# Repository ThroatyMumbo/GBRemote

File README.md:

# (WIP) Universal Remote cartridge for Game Boy

A cartridge that lets you turn your Game Boy into many different things.
A game controller? A Bluetooth gamepad? A Bluetooth receiver? A tooth brush? Whatever your heart desires!

YouTube video: https://youtu.be/3ZZjWmHPqLs

Both the hardware and core GBC firmware is based on Shilga's Croco Cart:
- https://github.com/shilga/rp2350-gameboy-cartridge-firmware/
- https://github.com/shilga/rp-gameboy-cartridge-hw

## Building

Needs [GBDK-2020](https://github.com/gbdk-2020/gbdk-2020), the [Pico SDK](https://github.com/raspberrypi/pico-sdk) and Python 3.

```
python3 -m venv .venv && .venv/bin/pip install numpy
make -C rom GBDK_HOME=/path/to/gbdk
PICO_SDK_PATH=/path/to/pico-sdk cmake -S firmware -B firmware/build
cmake --build firmware/build
```

The first `make` builds the Game Boy ROM and embeds it in the firmware (`firmware/generated/rom.h`), so rebuild both after changing the ROM.

## Flashing

Hold the BOOTSEL button (`SW2`) while plugging the cartridge's micro-USB port into your computer, then either copy `firmware/build/gbc_controller.uf2` to the drive that appears or run:

```
picotool load -x firmware/build/gbc_controller.uf2
```

## Loading Game Boy ROMs for the Transfer Pak

The N64 driver can act as a Transfer Pak holding a Game Boy ROM stored in the cart's flash. Put the cart in BOOTSEL as above, then:

```
tools/slot.sh 1 game.gbc
```

Pick the game under Controllers → Nintendo 64 → Transfer Pak. Slots 1-6 hold up to 2 MB each and slot 7 up to 1.75 MB; loading one slot leaves the others alone. An optional third argument sets the name shown on the Game Boy.

## Screenshots

| Controller select | Gamepad | Button mapping |
|:---:|:---:|:---:|
|  |  |  |
| **N64 Transfer Pak** | **Dreamcast VMU** | |
|  |  | |

## FAQ

### What the hell is this?

It's a Game Boy cartridge with a bunch of stuff attached to it. USB, Bluetooth, WiFi, IR, even a generic 12-pin controller port via USB-C.

### Is this a flash cart?

Sort of. It can be used as a flash cart, although that isn't the intended purpose. It's more meant for turning a Game Boy Color into a multipurpose remote of sorts.
Plus the onboard flash is 16 MB, which is only enough for like 10 GBC games.

### Where are all those cool demos you showed in the video?

Most of them I probably won't publish since they involve modding existing commercial games, which is messy to maintain in a public repo.
However, original stuff like "Shellack!" will be published at some point when I get a chance to clean it up.

### Does this work on a regular Game Boy? What about Game Boy Advance?

- Regular Game Boy is a maybe. It doesn't physically fit, but you can cleverly bypass this using a Game Shark. However when I tried this myself it just sits on a blank screen. Haven't troubleshooted this problem.
- It does work on a Game Boy Advance

### Where do I buy this?

You can't, at least not directly. This repo contains the production files for the cartridge and adapter PCBs that you can send off to your favorite PCB manufacturing site, but I warn you it'll likely be very expensive (~$500+). Getting just two of these cartridges + 10 adapters made took a couple weeks and lots of back and forth with JLCPCB. Not to mention the tedium of wiring all those controller adapters. I wouldn't recommend it unless you have time and money to burn.

### Will you sell these at some point?

Maybe? Like every project of mine, this is really more of a novelty than something that's practically useful, so I don't see myself ordering hundreds of these and selling them on Ko-fi anytime soon. More likely a very limited run as some special merch or something.

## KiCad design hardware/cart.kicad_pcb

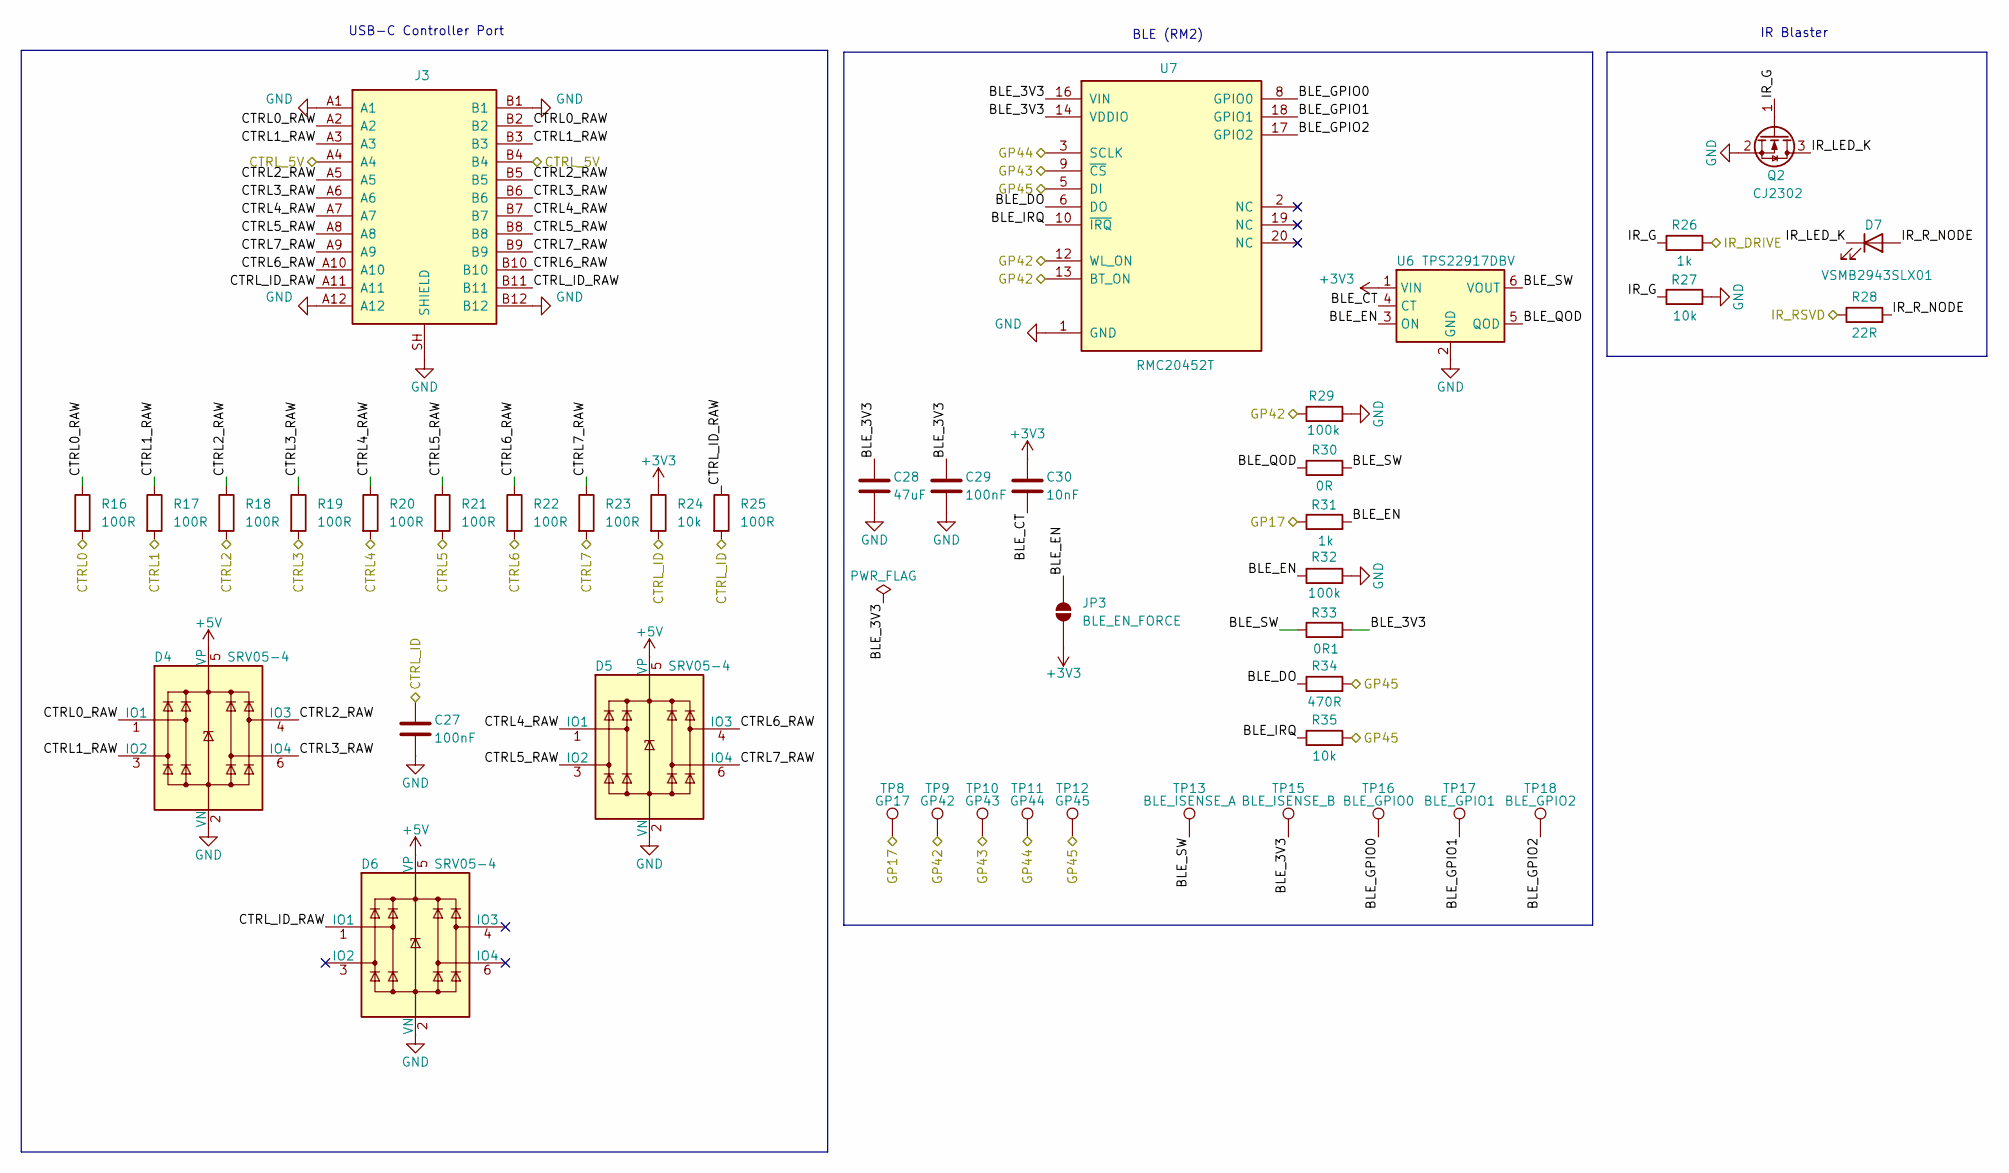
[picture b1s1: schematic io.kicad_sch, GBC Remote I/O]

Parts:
C27, C29: 100nF; C_0402_1005Metric; LCSC C1525
C28: 47uF; C_1206_3216Metric; LCSC C96123
C30: 10nF; C_0402_1005Metric; LCSC C15195
D4, D5, D6: SRV05-4; SOT-23-6; LCSC C13612
D7: VSMB2943SLX01; LED_Vishay_VSMB2943SL; LCSC C511094
J3: 12401610E4#2A; USB_C_Receptacle_Amphenol_12401610E4-2A; LCSC C5119948
JP3: BLE_EN_FORCE; SolderJumper-2_P1.3mm_Open_RoundedPad1.0x1.5mm
Q2: CJ2302; SOT-23; LCSC C8548
R16, R17, R18, R19, R20, R21, R22, R23, R25: 100R; R_0402_1005Metric; LCSC C25076
R24, R27, R35: 10k; R_0402_1005Metric; LCSC C25744
R26, R31: 1k; R_0402_1005Metric; LCSC C11702
R28: 22R; R_1206_3216Metric; LCSC C17958
R29, R32: 100k; R_0402_1005Metric; LCSC C25741
R30: 0R; R_0402_1005Metric; LCSC C17168
R33: 0R1; R_1206_3216Metric; LCSC C25334
R34: 470R; R_0402_1005Metric; LCSC C25117
TP8: GP17; TestPoint_Pad_D1.0mm
TP9: GP42; TestPoint_Pad_D1.0mm
TP10: GP43; TestPoint_Pad_D1.0mm
TP11: GP44; TestPoint_Pad_D1.0mm
TP12: GP45; TestPoint_Pad_D1.0mm
TP13: BLE_ISENSE_A; TestPoint_Pad_D1.0mm
TP15: BLE_ISENSE_B; TestPoint_Pad_D1.0mm
TP16: BLE_GPIO0; TestPoint_Pad_D1.0mm
TP17: BLE_GPIO1; TestPoint_Pad_D1.0mm
TP18: BLE_GPIO2; TestPoint_Pad_D1.0mm
U6: TPS22917DBV; SOT-23-6; LCSC C2681320
U7: RMC20452T; RaspberryPi_RM2; LCSC C49451547

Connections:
+3V3: C30.1, JP3.1 (A), R24.1, U6.1 (VIN); also elsewhere on the board
+5V: D4.5 (VP), D5.5 (VP), D6.5 (VP); also elsewhere on the board
/CTRL0: R16.2; also elsewhere on the board
/CTRL1: R17.2; also elsewhere on the board
/CTRL2: R18.2; also elsewhere on the board
/CTRL3: R19.2; also elsewhere on the board
/CTRL4: R20.2; also elsewhere on the board
/CTRL5: R21.2; also elsewhere on the board
/CTRL6: R22.2; also elsewhere on the board
/CTRL7: R23.2; also elsewhere on the board
/CTRL_5V: J3.A4, J3.B4; also elsewhere on the board
/CTRL_ID: C27.1, R24.2, R25.2; also elsewhere on the board
/Controller Port, IR, BLE/BLE_3V3: C28.1, C29.1, R33.2, TP15.1, U7.14 (VDDIO), U7.16 (VIN)
/Controller Port, IR, BLE/BLE_CT: C30.2, U6.4 (CT)
/Controller Port, IR, BLE/BLE_DO: R34.1, U7.6 (DO)
/Controller Port, IR, BLE/BLE_EN: JP3.2 (B), R31.2, R32.1, U6.3 (ON)
/Controller Port, IR, BLE/BLE_GPIO0: TP16.1, U7.8 (GPIO0)
/Controller Port, IR, BLE/BLE_GPIO1: TP17.1, U7.18 (GPIO1)
/Controller Port, IR, BLE/BLE_GPIO2: TP18.1, U7.17 (GPIO2)
/Controller Port, IR, BLE/BLE_IRQ: R35.1, U7.10 (~IRQ)
/Controller Port, IR, BLE/BLE_QOD: R30.1, U6.5 (QOD)
/Controller Port, IR, BLE/BLE_SW: R30.2, R33.1, TP13.1, U6.6 (VOUT)
/Controller Port, IR, BLE/CTRL0_RAW: D4.1 (IO1), J3.A2, J3.B2, R16.1
/Controller Port, IR, BLE/CTRL1_RAW: D4.3 (IO2), J3.A3, J3.B3, R17.1
/Controller Port, IR, BLE/CTRL2_RAW: D4.4 (IO3), J3.A5, J3.B5, R18.1
/Controller Port, IR, BLE/CTRL3_RAW: D4.6 (IO4), J3.A6, J3.B6, R19.1
/Controller Port, IR, BLE/CTRL4_RAW: D5.1 (IO1), J3.A7, J3.B7, R20.1
/Controller Port, IR, BLE/CTRL5_RAW: D5.3 (IO2), J3.A8, J3.B8, R21.1
/Controller Port, IR, BLE/CTRL6_RAW: D5.4 (IO3), J3.A10, J3.B10, R22.1
/Controller Port, IR, BLE/CTRL7_RAW: D5.6 (IO4), J3.A9, J3.B9, R23.1
/Controller Port, IR, BLE/CTRL_ID_RAW: D6.1 (IO1), J3.A11, J3.B11, R25.1
/Controller Port, IR, BLE/IR_G: Q2.1 (G), R26.1, R27.1
/Controller Port, IR, BLE/IR_LED_K: D7.1 (K), Q2.3 (D)
/Controller Port, IR, BLE/IR_R_NODE: D7.2 (A), R28.2
/GP17: R31.1, TP8.1; also elsewhere on the board
/GP42: R29.1, TP9.1, U7.12 (WL_ON), U7.13 (BT_ON); also elsewhere on the board
/GP43: TP10.1, U7.9 (~CS); also elsewhere on the board
/GP44: TP11.1, U7.3 (SCLK); also elsewhere on the board
/GP45: R34.2, R35.2, TP12.1, U7.5 (DI); also elsewhere on the board
/IR_DRIVE: R26.2; also elsewhere on the board
/IR_RSVD: R28.1; also elsewhere on the board
GND: C27.2, C28.2, C29.2, D4.2 (VN), D5.2 (VN), D6.2 (VN), J3.A1, J3.A12, J3.B1, J3.B12, J3.SH (SHIELD), Q2.2 (S), R27.2, R29.2, R32.2, U6.2 (GND), U7.1 (GND), U7.4 (GND), U7.7 (GND), U7.11 (GND), U7.15 (GND), U7.21 (GND); also elsewhere on the board

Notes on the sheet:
IR Blaster
BLE (RM2)
USB-C Controller Port

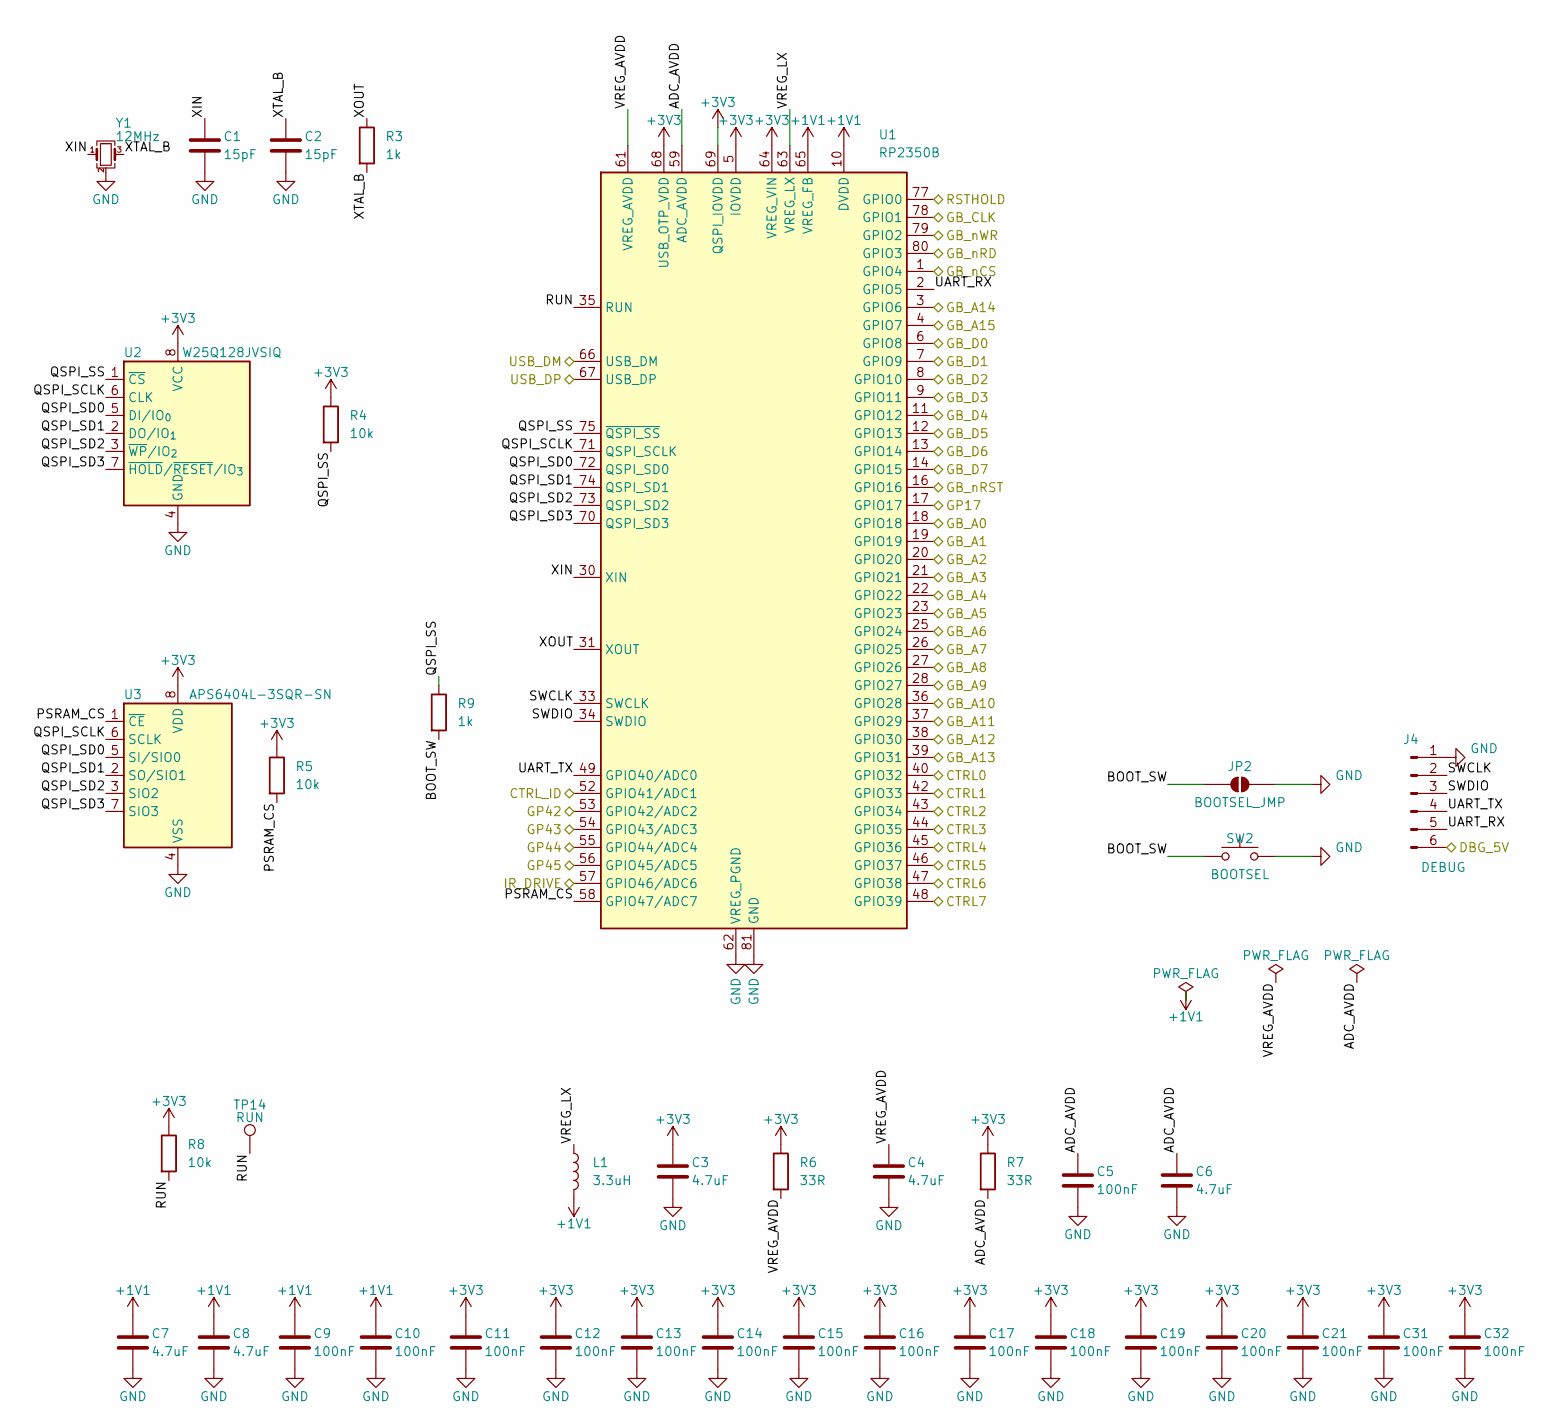
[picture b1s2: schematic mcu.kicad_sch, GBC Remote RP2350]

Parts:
C1, C2: 15pF; C_0402_1005Metric; LCSC C1548
C3, C4, C6, C7, C8: 4.7uF; C_0402_1005Metric; LCSC C23733
C5, C9, C10, C11, C12, C13, C14, C15, C16, C17, C18, C19, C20, C21, C31, C32: 100nF; C_0402_1005Metric; LCSC C1525
J4: DEBUG; JST_SH_SM06B-SRSS-TB_1x06-1MP_P1.00mm_Horizontal; LCSC C160405
JP2: BOOTSEL_JMP; SolderJumper-2_P1.3mm_Open_RoundedPad1.0x1.5mm
L1: 3.3uH; L_Murata_DFE201610P; LCSC C42411119
R3, R9: 1k; R_0402_1005Metric; LCSC C11702
R4, R5, R8: 10k; R_0402_1005Metric; LCSC C25744
R6, R7: 33R; R_0402_1005Metric; LCSC C25105
SW2: BOOTSEL; SW_SPST_PTS810; LCSC C116501
TP14: RUN; TestPoint_Pad_D1.0mm
U1: RP2350B; QFN-80-1EP_10x10mm_P0.4mm_EP3.4x3.4mm_ThermalVias; LCSC C42415655
U2: W25Q128JVSIQ; SOIC-8_5.3x5.3mm_P1.27mm; LCSC C97521
U3: APS6404L-3SQR-SN; SOIC-8_3.9x4.9mm_P1.27mm; LCSC C5333729
Y1: 12MHz; Crystal_SMD_3225-4Pin_3.2x2.5mm; LCSC C20625731

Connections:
+1V1: C7.1, C8.1, C9.1, C10.1, L1.2, U1.10 (DVDD), U1.32 (DVDD), U1.51 (DVDD), U1.65 (VREG_FB); also elsewhere on the board
+3V3: C3.1, C11.1, C12.1, C13.1, C14.1, C15.1, C16.1, C17.1, C18.1, C19.1, C20.1, C21.1, C31.1, C32.1, R4.1, R5.1, R6.1, R7.1, R8.1, U1.5 (IOVDD), U1.15 (IOVDD), U1.24 (IOVDD), U1.29 (IOVDD), U1.41 (IOVDD), U1.50 (IOVDD), U1.60 (IOVDD), U1.64 (VREG_VIN), U1.68 (USB_OTP_VDD), U1.69 (QSPI_IOVDD), U1.76 (IOVDD), U2.8 (VCC), U3.8 (VDD); also elsewhere on the board
/CTRL0: U1.40 (GPIO32); also elsewhere on the board
/CTRL1: U1.42 (GPIO33); also elsewhere on the board
/CTRL2: U1.43 (GPIO34); also elsewhere on the board
/CTRL3: U1.44 (GPIO35); also elsewhere on the board
/CTRL4: U1.45 (GPIO36); also elsewhere on the board
/CTRL5: U1.46 (GPIO37); also elsewhere on the board
/CTRL6: U1.47 (GPIO38); also elsewhere on the board
/CTRL7: U1.48 (GPIO39); also elsewhere on the board
/CTRL_ID: U1.52 (GPIO41/ADC1); also elsewhere on the board
/DBG_5V: J4.6; also elsewhere on the board
/GB_A0: U1.18 (GPIO18); also elsewhere on the board
/GB_A1: U1.19 (GPIO19); also elsewhere on the board
/GB_A2: U1.20 (GPIO20); also elsewhere on the board
/GB_A3: U1.21 (GPIO21); also elsewhere on the board
/GB_A4: U1.22 (GPIO22); also elsewhere on the board
/GB_A5: U1.23 (GPIO23); also elsewhere on the board
/GB_A6: U1.25 (GPIO24); also elsewhere on the board
/GB_A7: U1.26 (GPIO25); also elsewhere on the board
/GB_A8: U1.27 (GPIO26); also elsewhere on the board
/GB_A9: U1.28 (GPIO27); also elsewhere on the board
/GB_A10: U1.36 (GPIO28); also elsewhere on the board
/GB_A11: U1.37 (GPIO29); also elsewhere on the board
/GB_A12: U1.38 (GPIO30); also elsewhere on the board
/GB_A13: U1.39 (GPIO31); also elsewhere on the board
/GB_A14: U1.3 (GPIO6); also elsewhere on the board
/GB_A15: U1.4 (GPIO7); also elsewhere on the board
/GB_CLK: U1.78 (GPIO1); also elsewhere on the board
/GB_D0: U1.6 (GPIO8); also elsewhere on the board
/GB_D1: U1.7 (GPIO9); also elsewhere on the board
/GB_D2: U1.8 (GPIO10); also elsewhere on the board
/GB_D3: U1.9 (GPIO11); also elsewhere on the board
/GB_D4: U1.11 (GPIO12); also elsewhere on the board
/GB_D5: U1.12 (GPIO13); also elsewhere on the board
/GB_D6: U1.13 (GPIO14); also elsewhere on the board
/GB_D7: U1.14 (GPIO15); also elsewhere on the board
/GB_nCS: U1.1 (GPIO4); also elsewhere on the board
/GB_nRD: U1.80 (GPIO3); also elsewhere on the board
/GB_nRST: U1.16 (GPIO16); also elsewhere on the board
/GB_nWR: U1.79 (GPIO2); also elsewhere on the board
/GP17: U1.17 (GPIO17); also elsewhere on the board
/GP42: U1.53 (GPIO42/ADC2); also elsewhere on the board
/GP43: U1.54 (GPIO43/ADC3); also elsewhere on the board
/GP44: U1.55 (GPIO44/ADC4); also elsewhere on the board
/GP45: U1.56 (GPIO45/ADC5); also elsewhere on the board
/IR_DRIVE: U1.57 (GPIO46/ADC6); also elsewhere on the board
/MCU/ADC_AVDD: C5.1, C6.1, R7.2, U1.59 (ADC_AVDD)
/MCU/BOOT_SW: JP2.1 (A), R9.2, SW2.1
/MCU/PSRAM_CS: R5.2, U1.58 (GPIO47/ADC7), U3.1 (~CE)
/MCU/QSPI_SCLK: U1.71 (QSPI_SCLK), U2.6 (CLK), U3.6 (SCLK)
/MCU/QSPI_SD0: U1.72 (QSPI_SD0), U2.5 (DI/IO_{0}), U3.5 (SI/SIO0)
/MCU/QSPI_SD1: U1.74 (QSPI_SD1), U2.2 (DO/IO_{1}), U3.2 (SO/SIO1)
/MCU/QSPI_SD2: U1.73 (QSPI_SD2), U2.3 (~WP/IO_{2}), U3.3 (SIO2)
/MCU/QSPI_SD3: U1.70 (QSPI_SD3), U2.7 (~HOLD/~RESET/IO_{3}), U3.7 (SIO3)
/MCU/QSPI_SS: R4.2, R9.1, U1.75 (~QSPI_SS), U2.1 (~CS)
/MCU/RUN: R8.2, TP14.1, U1.35 (RUN)
/MCU/SWCLK: J4.2, U1.33 (SWCLK)
/MCU/SWDIO: J4.3, U1.34 (SWDIO)
/MCU/UART_RX: J4.5, U1.2 (GPIO5)
/MCU/UART_TX: J4.4, U1.49 (GPIO40/ADC0)
/MCU/VREG_AVDD: C4.1, R6.2, U1.61 (VREG_AVDD)
/MCU/VREG_LX: L1.1, U1.63 (VREG_LX)
/MCU/XIN: C1.1, U1.30 (XIN), Y1.1
/MCU/XOUT: R3.1, U1.31 (XOUT)
/MCU/XTAL_B: C2.1, R3.2, Y1.3
/RSTHOLD: U1.77 (GPIO0); also elsewhere on the board
/USB_DM: U1.66 (USB_DM); also elsewhere on the board
/USB_DP: U1.67 (USB_DP); also elsewhere on the board
GND: C1.2, C2.2, C3.2, C4.2, C5.2, C6.2, C7.2, C8.2, C9.2, C10.2, C11.2, C12.2, C13.2, C14.2, C15.2, C16.2, C17.2, C18.2, C19.2, C20.2, C21.2, C31.2, C32.2, J4.1, JP2.2 (B), SW2.2, U1.62 (VREG_PGND), U1.81 (GND), U2.4 (GND), U3.4 (VSS), Y1.2 (G), Y1.4 (G); also elsewhere on the board

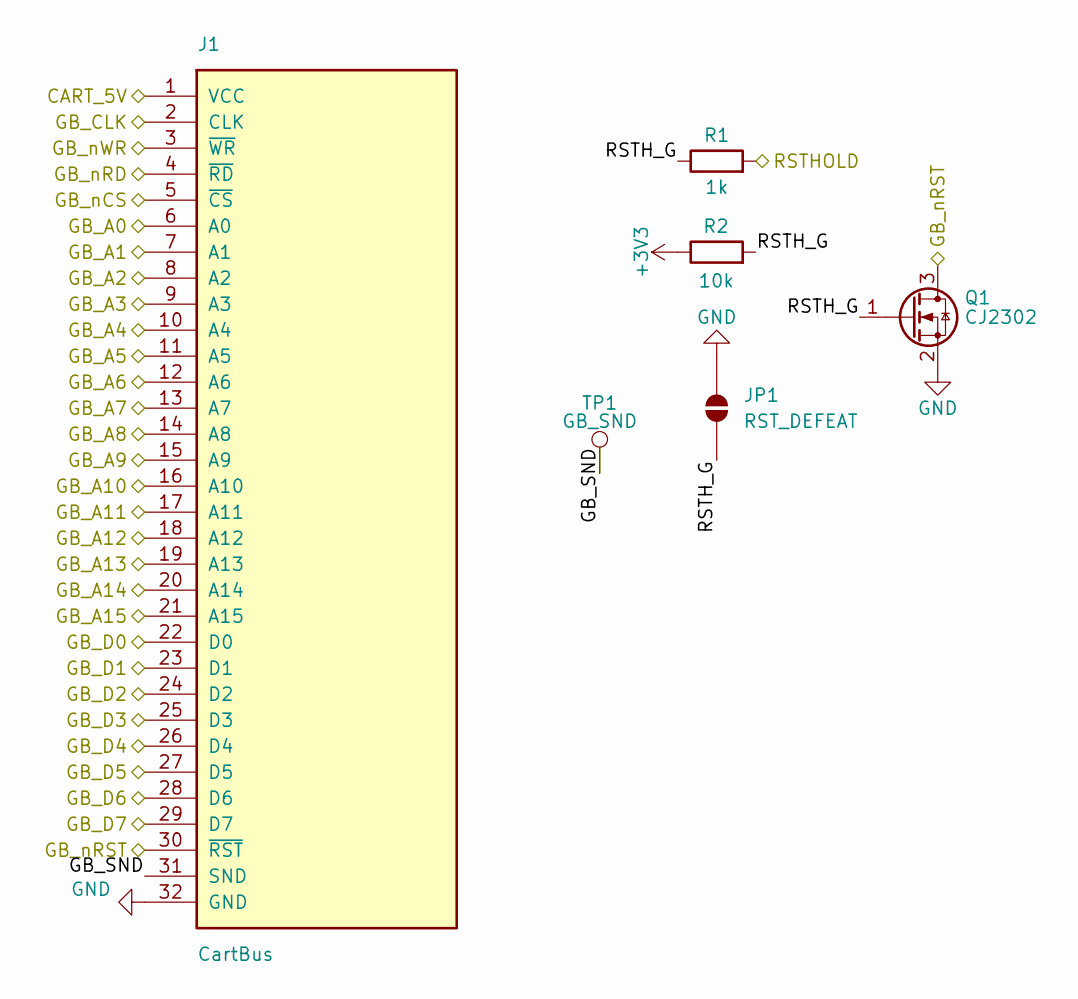
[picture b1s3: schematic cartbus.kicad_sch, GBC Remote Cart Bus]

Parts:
J1: CartBus; GameBoy_Cartridge_EdgeConnector
JP1: RST_DEFEAT; SolderJumper-2_P1.3mm_Open_RoundedPad1.0x1.5mm
Q1: CJ2302; SOT-23; LCSC C8548
R1: 1k; R_0402_1005Metric; LCSC C11702
R2: 10k; R_0402_1005Metric; LCSC C25744
TP1: GB_SND; TestPoint_Pad_D1.0mm

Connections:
+3V3: R2.1; also elsewhere on the board
/CART_5V: J1.1 (VCC); also elsewhere on the board
/Cart Bus/GB_SND: J1.31 (SND), TP1.1
/Cart Bus/RSTH_G: JP1.1 (A), Q1.1 (G), R1.1, R2.2
/GB_A0: J1.6 (A0); also elsewhere on the board
/GB_A1: J1.7 (A1); also elsewhere on the board
/GB_A2: J1.8 (A2); also elsewhere on the board
/GB_A3: J1.9 (A3); also elsewhere on the board
/GB_A4: J1.10 (A4); also elsewhere on the board
/GB_A5: J1.11 (A5); also elsewhere on the board
/GB_A6: J1.12 (A6); also elsewhere on the board
/GB_A7: J1.13 (A7); also elsewhere on the board
/GB_A8: J1.14 (A8); also elsewhere on the board
/GB_A9: J1.15 (A9); also elsewhere on the board
/GB_A10: J1.16 (A10); also elsewhere on the board
/GB_A11: J1.17 (A11); also elsewhere on the board
/GB_A12: J1.18 (A12); also elsewhere on the board
/GB_A13: J1.19 (A13); also elsewhere on the board
/GB_A14: J1.20 (A14); also elsewhere on the board
/GB_A15: J1.21 (A15); also elsewhere on the board
/GB_CLK: J1.2 (CLK); also elsewhere on the board
/GB_D0: J1.22 (D0); also elsewhere on the board
/GB_D1: J1.23 (D1); also elsewhere on the board
/GB_D2: J1.24 (D2); also elsewhere on the board
/GB_D3: J1.25 (D3); also elsewhere on the board
/GB_D4: J1.26 (D4); also elsewhere on the board
/GB_D5: J1.27 (D5); also elsewhere on the board
/GB_D6: J1.28 (D6); also elsewhere on the board
/GB_D7: J1.29 (D7); also elsewhere on the board
/GB_nCS: J1.5 (~CS); also elsewhere on the board
/GB_nRD: J1.4 (~RD); also elsewhere on the board
/GB_nRST: J1.30 (~RST), Q1.3 (D); also elsewhere on the board
/GB_nWR: J1.3 (~WR); also elsewhere on the board
/RSTHOLD: R1.2; also elsewhere on the board
GND: J1.32 (GND), JP1.2 (B), Q1.2 (S); also elsewhere on the board

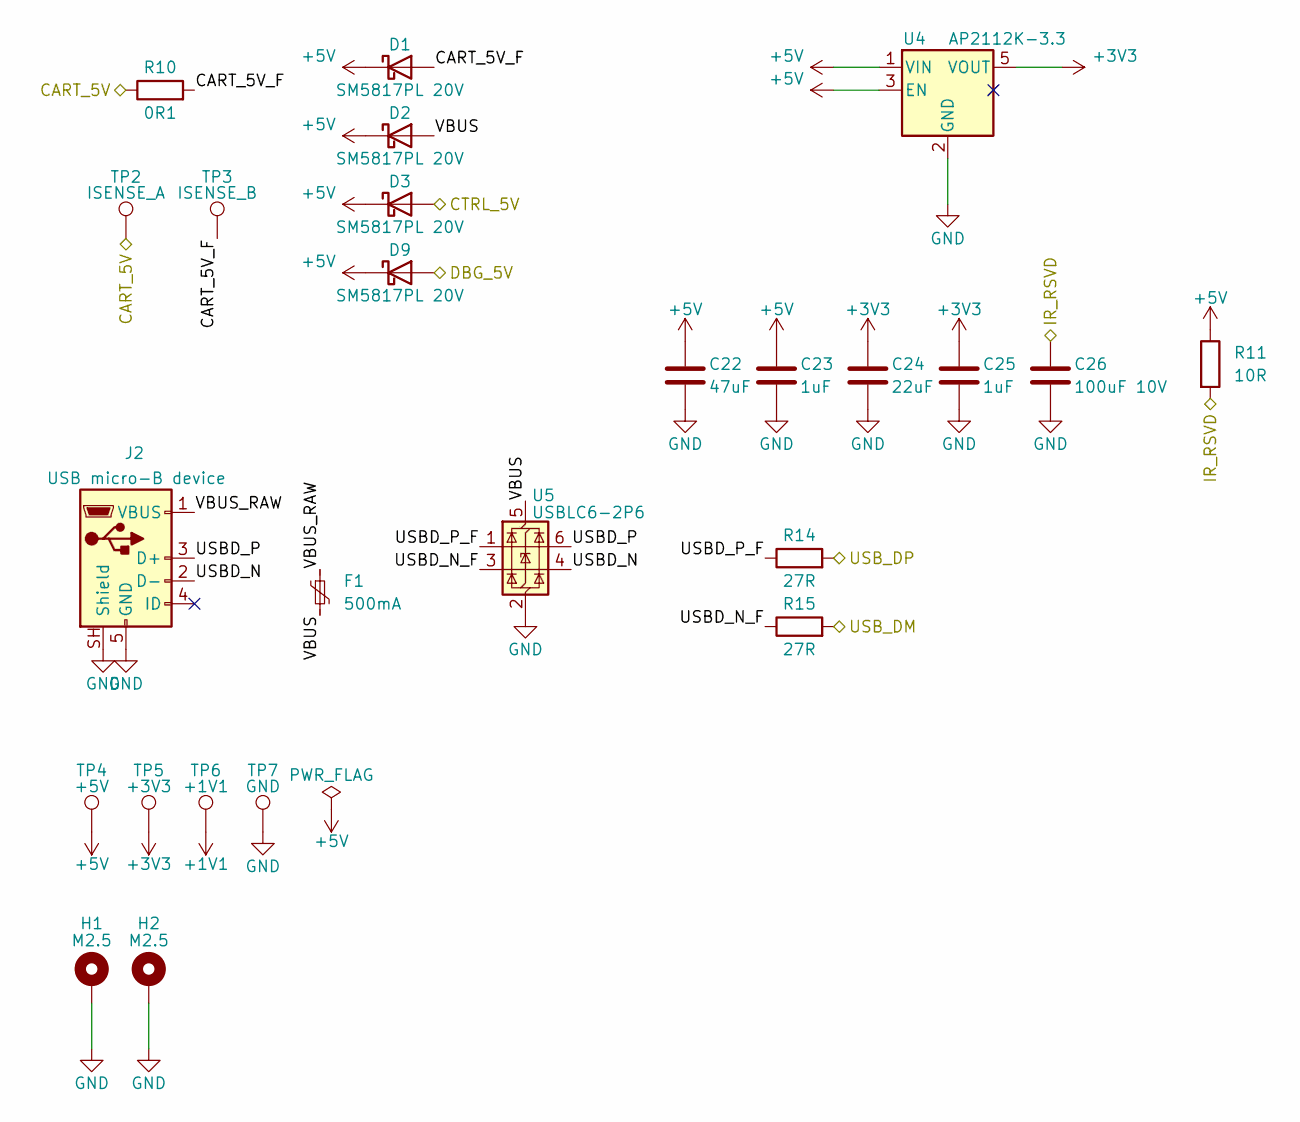
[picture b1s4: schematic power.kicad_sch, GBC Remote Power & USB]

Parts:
C22: 47uF; C_1210_3225Metric; LCSC C2932478
C23, C25: 1uF; C_0402_1005Metric; LCSC C52923
C24: 22uF; C_0805_2012Metric; LCSC C45783
C26: 100uF 10V; C_1210_3225Metric; LCSC C23742
D1, D2, D3, D9: SM5817PL 20V; D_SOD-123F; LCSC C669022
F1: 500mA; Fuse_1206_3216Metric; LCSC C2649911
H1, H2: M2.5; MountingHole_2.7mm_M2.5_Pad
J2: USB micro-B device; USB_Micro-B_XKB_U254-051T-4BH83-F2S; LCSC C2682231
R10: 0R1; R_1206_3216Metric; LCSC C25334
R11: 10R; R_0402_1005Metric; LCSC C25077
R14, R15: 27R; R_0402_1005Metric; LCSC C25100
TP2: ISENSE_A; TestPoint_Pad_D1.0mm
TP3: ISENSE_B; TestPoint_Pad_D1.0mm
TP4: +5V; TestPoint_Pad_D1.0mm
TP5: +3V3; TestPoint_Pad_D1.0mm
TP6: +1V1; TestPoint_Pad_D1.0mm
TP7: GND; TestPoint_Pad_D1.0mm
U4: AP2112K-3.3; SOT-23-5; LCSC C51118
U5: USBLC6-2P6; SOT-666; LCSC C15999

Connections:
+1V1: TP6.1; also elsewhere on the board
+3V3: C24.1, C25.1, TP5.1, U4.5 (VOUT); also elsewhere on the board
+5V: C22.1, C23.1, D1.1 (K), D2.1 (K), D3.1 (K), D9.1 (K), R11.1, TP4.1, U4.1 (VIN), U4.3 (EN); also elsewhere on the board
/CART_5V: R10.1, TP2.1; also elsewhere on the board
/CTRL_5V: D3.2 (A); also elsewhere on the board
/DBG_5V: D9.2 (A); also elsewhere on the board
/IR_RSVD: C26.1, R11.2; also elsewhere on the board
/Power and USB/CART_5V_F: D1.2 (A), R10.2, TP3.1
/Power and USB/USBD_N: J2.2 (D-), U5.4 (I/O2)
/Power and USB/USBD_N_F: R15.1, U5.3 (I/O2)
/Power and USB/USBD_P: J2.3 (D+), U5.6 (I/O1)
/Power and USB/USBD_P_F: R14.1, U5.1 (I/O1)
/Power and USB/VBUS: D2.2 (A), F1.2, U5.5 (VBUS)
/Power and USB/VBUS_RAW: F1.1, J2.1 (VBUS)
/USB_DM: R15.2; also elsewhere on the board
/USB_DP: R14.2; also elsewhere on the board
GND: C22.2, C23.2, C24.2, C25.2, C26.2, H1.1, H2.1, J2.5 (GND), J2.SH (Shield), TP7.1, U4.2 (GND), U5.2 (GND); also elsewhere on the board

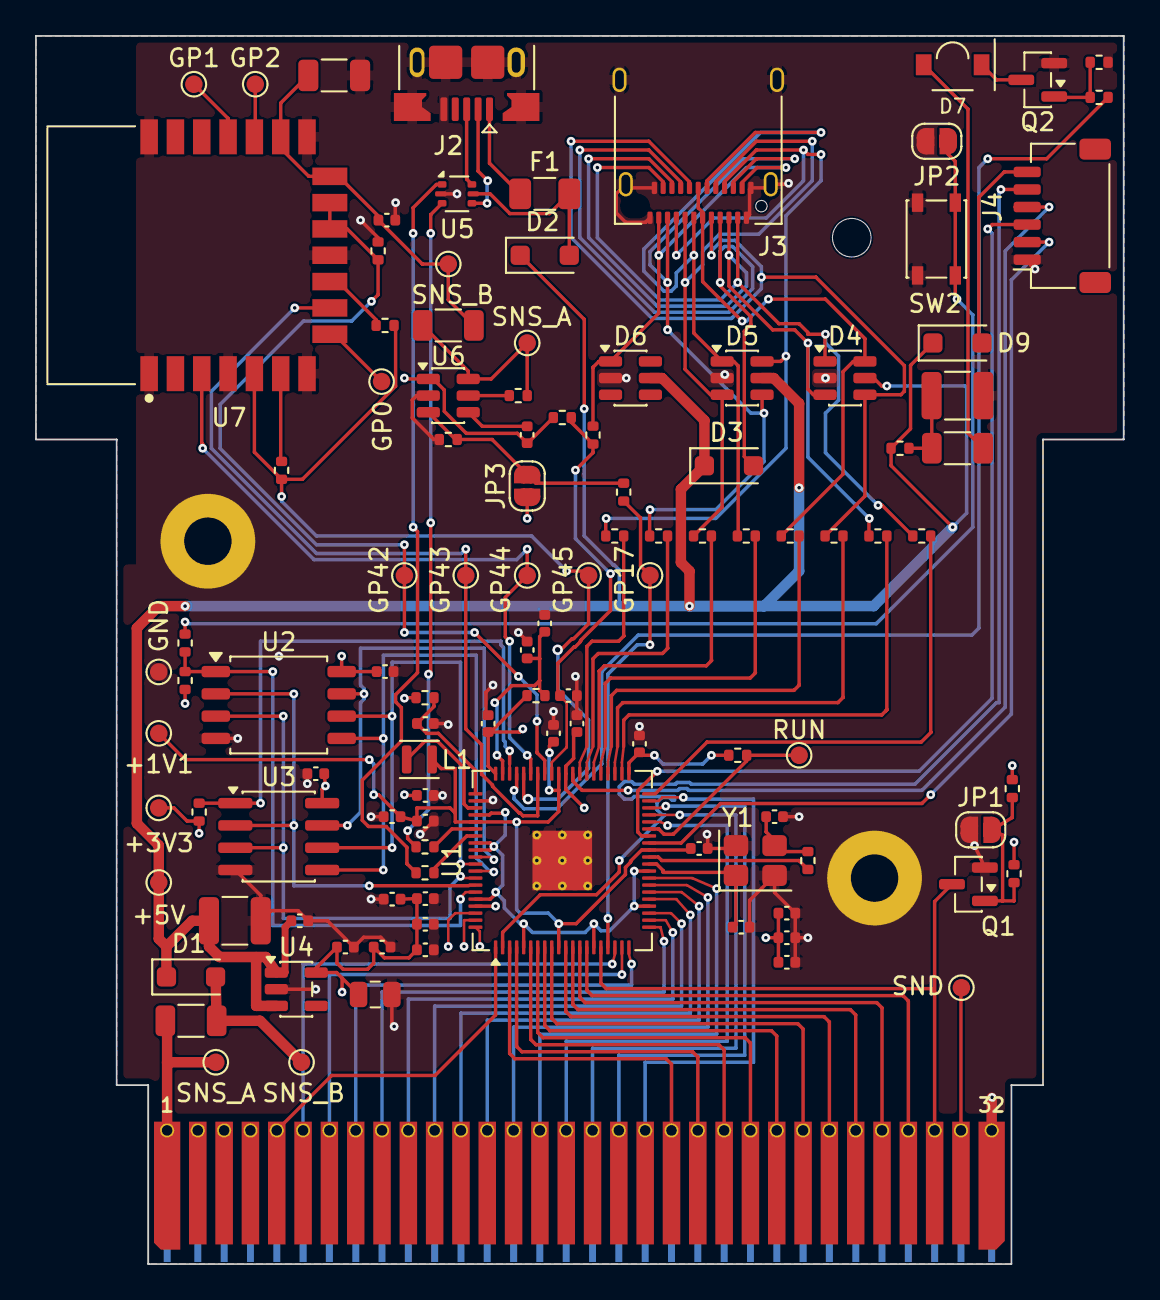
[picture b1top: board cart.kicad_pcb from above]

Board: 4 copper layers, 62.0 x 70.0 mm, 113 parts (0 on the bottom side), 105 nets.

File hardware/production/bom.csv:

Designator,Footprint,Quantity,Value,LCSC Part #
"C1, C2",0402,2,15pF,C1548
"C10, C11, C12, C13, C14, C15, C16, C17, C18, C19, C20, C21, C27, C29, C31, C32, C5, C9",0402,18,100nF,C1525
C22,1210,1,47uF,C2932478
"C23, C25",0402,2,1uF,C52923
C24,0805,1,22uF,C45783
C26,1210,1,100uF 10V,C23742
C28,1206,1,47uF,C96123
"C3, C4, C6, C7, C8",0402,5,4.7uF,C23733
C30,0402,1,10nF,C15195
"D1, D2, D3, D9",D_SOD-123F,4,SM5817PL 20V,C669022
"D4, D5, D6",SOT-23-6,3,SRV05-4,C13612
D7,LED_Vishay_VSMB2943SL,1,VSMB2943SLX01,C511094
F1,1206,1,500mA,C2649911
J1,GameBoy_Cartridge_EdgeConnector,1,CartBus,
J2,USB_Micro-B_XKB_U254-051T-4BH83-F2S,1,USB micro-B device,C2682231
J3,USB_C_Receptacle_Amphenol_12401610E4-2A,1,12401610E4#2A,C5119948
J4,JST_SH_SM06B-SRSS-TB_1x06-1MP_P1.00mm_Horizontal,1,DEBUG,C160405
L1,L_Murata_DFE201610P,1,3.3uH,C42411119
"Q1, Q2",SOT-23,2,CJ2302,C8548
"R1, R26, R3, R31, R9",0402,5,1k,C11702
"R10, R33",1206,2,0R1,C25334
R11,0402,1,10R,C25077
"R14, R15",0402,2,27R,C25100
"R16, R17, R18, R19, R20, R21, R22, R23, R25",0402,9,100R,C25076
"R2, R24, R27, R35, R4, R5, R8",0402,7,10k,C25744
R28,1206,1,22R,C17958
"R29, R32",0402,2,100k,C25741
R30,0402,1,0R,C17168
R34,0402,1,470R,C25117
"R6, R7",0402,2,33R,C25105
SW2,SW_SPST_PTS810,1,BOOTSEL,C116501
U1,QFN-80-1EP_10x10mm_P0.4mm_EP3.4x3.4mm_ThermalVias,1,RP2350B,C42415655
U2,SOIC-8_5.3x5.3mm_P1.27mm,1,W25Q128JVSIQ,C97521
U3,SOIC-8_3.9x4.9mm_P1.27mm,1,APS6404L-3SQR-SN,C5333729
U4,SOT-23-5,1,AP2112K-3.3,C51118
U5,SOT-666,1,USBLC6-2P6,C15999
U6,SOT-23-6,1,TPS22917DBV,C2681320
U7,RaspberryPi_RM2,1,RMC20452T,C49451547
Y1,Crystal_SMD_3225-4Pin_3.2x2.5mm,1,12MHz,C20625731

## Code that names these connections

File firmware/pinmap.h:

// pinmap.h — RP2350B (U1) GPIOs to cart edge J1 and controller port J3; check_sch.py diffs it
// against hardware/gen/expected_nets.txt. The cart bus stays at GP31 and below: one 32-bit mask.
#pragma once

#define PIN_RSTHOLD 0   // gate of the /RST hold FET        — output; HIGH = console held in reset
#define PIN_CLK   1     // GB CLK (timing reference)        — input
#define PIN_NWR   2     // GB /WR                           — input
#define PIN_NRD   3     // GB /RD  (read=low, write=high)   — input
#define PIN_NCS   4     // GB /CS                           — input (unused for ROM)
#define PIN_A14   6     // A14 — region gate (low/high bank)
#define PIN_A15   7     // A15 — internal-space gate ($8000+)
#define PIN_D0    8     // D0..D7 = GP8..GP15 (D0 = LSB)    — driven on reads
#define PIN_RST   16    // GB /reset                        — input; resets cart state
#define PIN_A0    18    // A0..A13 = GP18..GP31             — input

// wire_pos[i] = offset from PIN_A0 of the GPIO carrying A(i); the first suspect for a garbled logo.
// Banks are permuted at load; the mailbox paths un-permute via cs_wire_pos.
#define A0_13_WIRE_POS { 0, 1, 2, 3, 4, 5, 6, 7, 8, 9, 10, 11, 12, 13 }

// write_capture samples GP17 into bit 11, which nothing reads; the GP16/GP17 gap puts A0 at bit 12.

// Controller port CTRL0-7 = GP32-39, each behind 100R (R16-R23); reachable only from PIO2 at base 16.
#define PIN_CTRL0    32
#define PIN_CTRL_N   8
#define PIN_CTRL(n)  (PIN_CTRL0 + (n))

#define PIN_JOYBUS   PIN_CTRL0      // N64 Joybus data line

// Dreamcast Maple. Must be consecutive with SDCKA lower: the PIO reaches both with one
// `set pins,2`, and the decode reads them as bit0=SDCKA, bit1=SDCKB.
#define PIN_MAPLE_A  PIN_CTRL0      // DC connector pin 1
#define PIN_MAPLE_B  PIN_CTRL(1)    // DC connector pin 5

// SNES/NES. LATCH and CLK consecutive, LATCH lower: one IN base reaches both. DATA1 is the only
// driven line, open-drain.
#define PIN_SNES_DATA1  PIN_CTRL0   // SNES connector pin 4 / NES D0
#define PIN_SNES_DATA2  PIN_CTRL(1) // SNES pin 5 — fitted, outside ctrl_mask: Hi-Z reads as no joypad 3
#define PIN_SNES_LATCH  PIN_CTRL(2) // SNES pin 3
#define PIN_SNES_CLK    PIN_CTRL(3) // SNES pin 2
#define PIN_SNES_IOBIT  PIN_CTRL(4) // SNES pin 6 — fitted, outside ctrl_mask, reserved

// Genesis / Mega Drive DE-9. Seven signals, CTRL7 left free. Two adjacency rules, one per state
// machine: D0-D3 must be consecutive for `out pindirs,4` and TL/TR consecutive for `out pindirs,2`.
#define PIN_GEN_TL   PIN_CTRL0      // DB9 pin 6 — D4: B while TH high, A while low
#define PIN_GEN_TR   PIN_CTRL(1)    // DB9 pin 9 — D5: C while TH high, START while low
#define PIN_GEN_TH   PIN_CTRL(2)    // DB9 pin 7 — console output. `wait n pin 0` and `jmp pin`
#define PIN_GEN_D0   PIN_CTRL(3)    // D0-D3 = DB9 1-4: UP/DOWN/LEFT/RIGHT, or Z/Y/X/MODE on cycle 7

#define PIN_CTRL_ID  41             // cable ID divider: R24 10k to +3V3, R_id in the adapter shell
#define CTRL_ID_ADC  1              // ADC input 1 (RP2350B: ADC0..7 = GP40..47)

#define PIN_BLE_EN   17             // U6 load switch on the RM2's 3V3; R32 holds it off on a cold board

#define PIN_IR_TX    46             // IR_DRIVE: high turns Q on and lights the LED; R27 holds it off

// Also taken, no pin spare: GP5/GP40 UART1 (J4), GP42-45 RM2 gSPI, GP47 PSRAM CS (U3).
